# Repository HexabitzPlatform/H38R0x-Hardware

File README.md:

# H38R0x-Hardware

Hexabitz Isolated Bipolar 15V DC-DC Power Module Hardware Design

Redesign this module and check for any errors in the previous design. No MCU is required; remove UART ports.

This design must use two hexagons with a 2-layer PCB stack-up.

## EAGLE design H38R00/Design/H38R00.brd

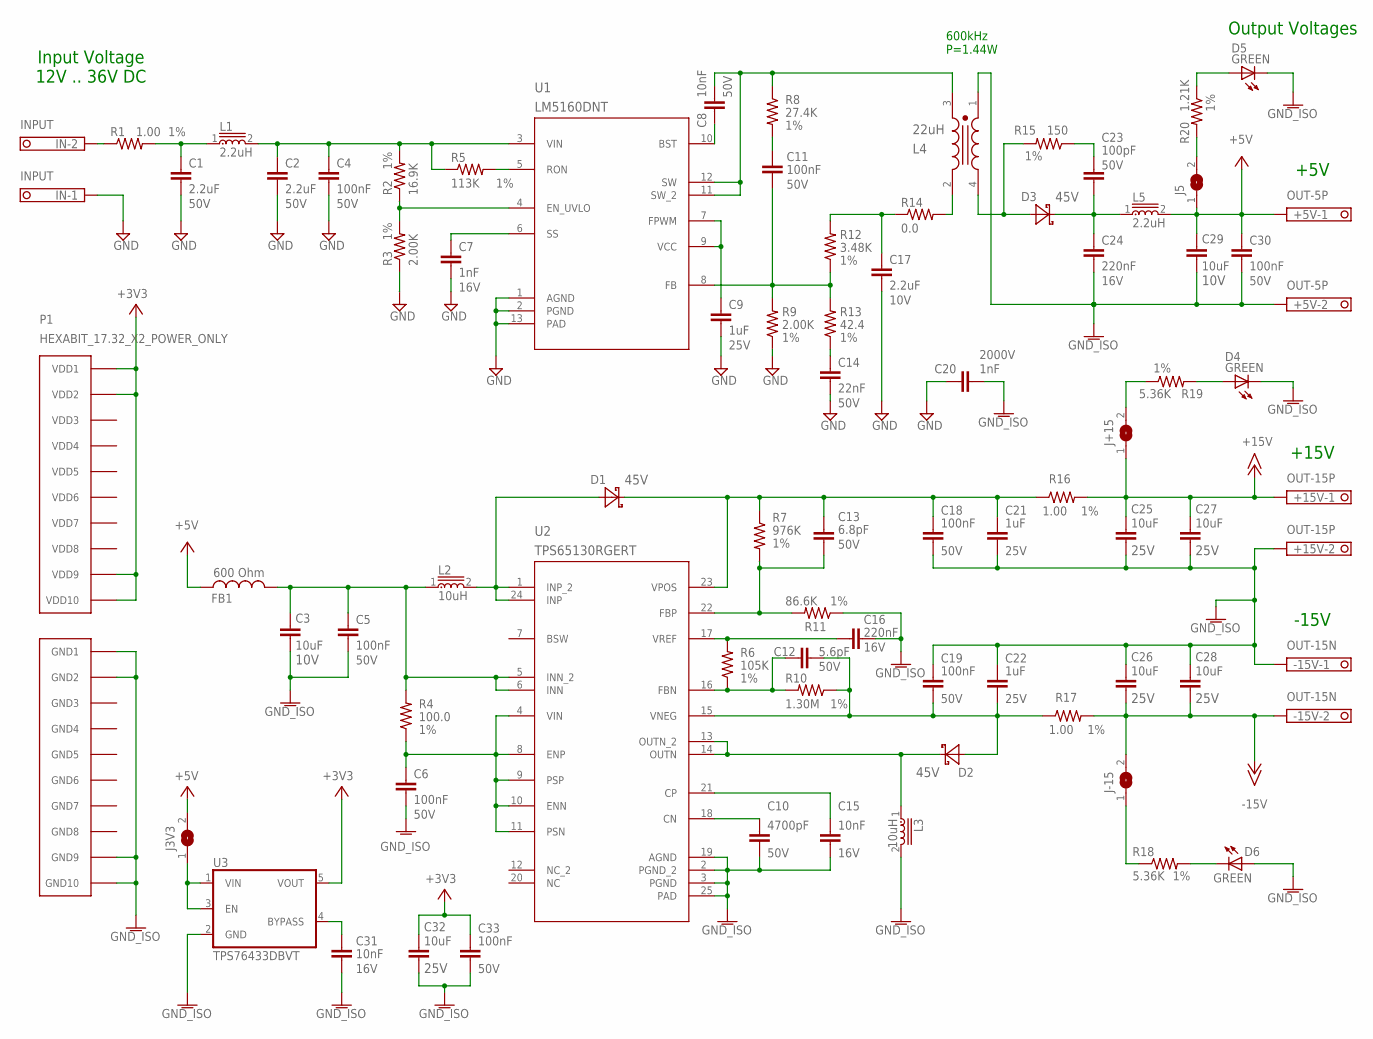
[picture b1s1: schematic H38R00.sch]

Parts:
+5V: OUT-5P; CON-PHOENIX-350_1751248
+15V: OUT-15P; CON-PHOENIX-350_1751248
-15V: OUT-15N; CON-PHOENIX-350_1751248
C1, C2: 2.2uF; C1206K; VOLTAGE 50V; MPN UMK316B7225KD-T
C3, C29: 10uF; C-0805; TOLERANCE 10%; VOLTAGE_RATING 10V; MPN 885012207026
C4, C5, C6, C11, C18, C19, C30, C33: 100nF; C-0603; TOLERANCE 10%; VOLTAGE_RATING 50V; MPN C1608X7R1H104K
C7: 1nF; C-0603; TOLERANCE 10%; VOLTAGE_RATING 16V; MPN 885012206034
C8: 10nF; C-0603; TOLERANCE 10%; VOLTAGE_RATING 50V; MPN C0603C103J5RACTU
C9, C21, C22: 1uF; C-0603; TOLERANCE 10%; VOLTAGE_RATING 25V; MPN TMK107B7105KA-T
C10: 4700pF; C-0603; TOLERANCE 10%; VOLTAGE_RATING 50V; MPN 885012206087
C12: 5.6pF; C-0603; TOLERANCE 5%; VOLTAGE_RATING 50V; MPN 06035A5R6CAT2A
C13: 6.8pF; C-0603; TOLERANCE 10%; VOLTAGE_RATING 50V; MPN 06035A6R8CAT2A
C14: 22nF; C-0603; TOLERANCE 10%; VOLTAGE_RATING 50V; MPN GRM188R71H223KA01D
C15, C31: 10nF; C-0603; TOLERANCE 10%; VOLTAGE_RATING 16V; MPN 885012206040
C16, C24: 220nF; C-0603; TOLERANCE 10%; VOLTAGE_RATING 16V; MPN 885012206048
C17: 2.2uF; C-0603; TOLERANCE 10%; VOLTAGE_RATING 10V; MPN GRM188R71A225KE15D
C20: 1nF; C1206K; VOLTAGE 2000V; MPN 202R18W102KV4E
C23: 100pF; C-0603; TOLERANCE 5%; VOLTAGE_RATING 50V; MPN C0603C101J5GACTU
C25, C26, C27, C28, C32: 10uF; C-0805; TOLERANCE 10%; VOLTAGE_RATING 25V; MPN GRM21BC71E106KE11L
D1, D2, D3: DIOD-SOD-123; SOD123; VOLTAGE_RATING_DC 45V; MPN NTS245SFT1G
D4, D5, D6: GREEN; VLMS1300-GS08
FB1: 600 Ohm; FB-0603; MPN BLM18KG601SN1D
IN: INPUT; CON-PHOENIX-350_1751248
J3V3, J5: SJ
J+15: SJ
J-15: SJ
L1, L5: 2.2uH; C-0603
L2, L3: 10uH; WUERTH_ELEKTRONIK_74404024100_0
L4: 22uH; WUERTH_ELEKTRONIK_74489430220_0
P1: HEXABIT_17.32_X2_POWER_ONLY
R1, R16, R17: 1.00; R-0603; TOLERANCE 1%; MPN CRCW06031R00FKEA
R2: 16.9K; R-0603; TOLERANCE 1%; MPN CRCW060316K9FKEA
R3, R9: 2.00K; R-0603; TOLERANCE 1%; MPN CRCW06032K00FKEA
R4: 100.0; R-0603; TOLERANCE 1%; MPN CRCW0603100RFKEA
R5: 113K; R-0603; TOLERANCE 1%; MPN CRCW0603113KFKEA
R6: 105K; R-0603; TOLERANCE 1%; MPN CRCW0603105KFKEA
R7: 976K; R-0603; TOLERANCE 1%; MPN CRCW0603976KFKEA
R8: 27.4K; R-0603; TOLERANCE 1%; MPN CRCW060327K4FKEA
R10: 1.30M; R-0603; TOLERANCE 1%; MPN CRCW06031M30FKEA
R11: 86.6K; R-0603; TOLERANCE 1%; MPN CRCW060386K6FKEA
R12: 3.48K; R-0603; TOLERANCE 1%; MPN CRCW06033K48FKEA
R13: 42.4; R-0603; TOLERANCE 1%; MPN CRCW060342R2FKEA
R14: 0.0; R-0603; TOLERANCE 5%; MPN ERJ-3GEY0R00V
R15: 150; R-0603; TOLERANCE 1%; MPN CRCW0603150RFKEA
R18, R19: 5.36K; R-0603; TOLERANCE 1%; MPN CRCW06035K36FKEA
R20: 1.21K; R-0603; TOLERANCE 1%; MPN CRCW06031K21FKEA
U1: LM5160DNT; DNT0012B
U2: TPS65130RGERT; RGE0024B_NV
U3: TPS76433DBVT; SOT25

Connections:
+3V3: C32.1, C33.1, P1.PAD_PU11 (VDD1), P1.PAD_PU12 (VDD2), P1.PAD_PU19 (VDD9), P1.PAD_PU20 (VDD10), U3.5 (VOUT)
+5V: +5V.1, C29.1, C30.1, FB1.1, J3V3.2, J5.1, L5.2
+15V: +15V.1, C25.1, C27.1, J+15.1, R16.2
-15V: -15V.2, C26.2, C28.2, J-15.2, R17.2
GND: C1.2, C2.2, C4.2, C7.2, C9.2, C14.2, C17.2, C20.1, IN.1, R3.1, R9.1, U1.1 (AGND), U1.2 (PGND), U1.13 (PAD)
GND3: P1.PAD_PD13 (GND3)
GND4: P1.PAD_PD14 (GND4)
GND5: P1.PAD_PD15 (GND5)
GND6: P1.PAD_PD16 (GND6)
GND7: P1.PAD_PD17 (GND7)
GND8: P1.PAD_PD18 (GND8)
IGND: +5V.2, +15V.2, -15V.1, C3.2, C5.2, C6.2, C10.2, C15.2, C16.2, C18.2, C19.1, C20.2, C21.2, C22.1, C24.2, C25.2, C26.1, C27.2, C28.1, C29.2, C30.2, C31.2, C32.2, C33.2, D4.C, D5.C, D6.A, L3.2, L4.1, P1.PAD_PD11 (GND1), P1.PAD_PD12 (GND2), P1.PAD_PD19 (GND9), P1.PAD_PD20 (GND10), R11.1, U2.2 (PGND_2), U2.3 (PGND), U2.19 (AGND), U2.25 (PAD), U3.2 (GND)
unnamed: IN.2, R1.1
unnamed: C1.1, L1.1, R1.2
unnamed: C2.1, C4.1, L1.2, R2.2, R5.1, U1.3 (VIN)
unnamed: R5.2, U1.5 (RON)
unnamed: R2.1, R3.2, U1.4 (EN_UVLO)
unnamed: C7.1, U1.6 (SS)
unnamed: C8.2, L4.3, R8.1, U1.11 (SW_2), U1.12 (SW)
unnamed: C8.1, U1.10 (BST)
unnamed: C9.1, U1.7 (FPWM), U1.9 (VCC)
unnamed: C11.2, R9.2, R12.1, R13.2, U1.8 (FB)
unnamed: C11.1, R8.2
unnamed: C17.1, R12.2, R14.1
unnamed: L4.2, R14.2
unnamed: C14.1, R13.1
unnamed: C23.2, C24.1, D3.2 (C), L5.1
unnamed: D3.1 (A), L4.4, R15.2
unnamed: C23.1, R15.1
unnamed: C3.1, C5.1, FB1.2, L2.1, R4.2, U2.5 (INN_2), U2.6 (INN)
unnamed: J5.2, R20.2
unnamed: D5.A, R20.1
unnamed: D1.1 (A), L2.2, U2.1 (INP_2), U2.24 (INP)
unnamed: C13.2, C18.1, C21.1, D1.2 (C), R7.1, R16.1, U2.23 (VPOS)
unnamed: C6.1, R4.1, U2.4 (VIN), U2.8 (ENP), U2.9 (PSP), U2.10 (ENN), U2.11 (PSN)
unnamed: C10.1, U2.18 (CN)
unnamed: C15.1, U2.21 (CP)
unnamed: D2.2 (C), L3.1, U2.13 (OUTN_2), U2.14 (OUTN)
unnamed: C12.2, C19.2, C22.2, D2.1 (A), R10.1, R17.1, U2.15 (VNEG)
unnamed: C12.1, R6.1, R10.2, U2.16 (FBN)
unnamed: C16.1, R6.2, U2.17 (VREF)
unnamed: C13.1, R7.2, R11.2, U2.22 (FBP)
unnamed: J+15.2, R19.1
unnamed: D4.A, R19.2
unnamed: J-15.1, R18.1
unnamed: D6.C, R18.2
unnamed: C31.1, U3.4 (BYPASS)
unnamed: J3V3.1, U3.1 (VIN), U3.3 (EN)
VDD3: P1.PAD_PU13 (VDD3)
VDD4: P1.PAD_PU14 (VDD4)
VDD5: P1.PAD_PU15 (VDD5)
VDD6: P1.PAD_PU16 (VDD6)
VDD7: P1.PAD_PU17 (VDD7)
VDD8: P1.PAD_PU18 (VDD8)

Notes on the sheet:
Input Voltage 12V .. 36V DC
600kHz P=1.44W
Output Voltages
+5V
+15V
-15V

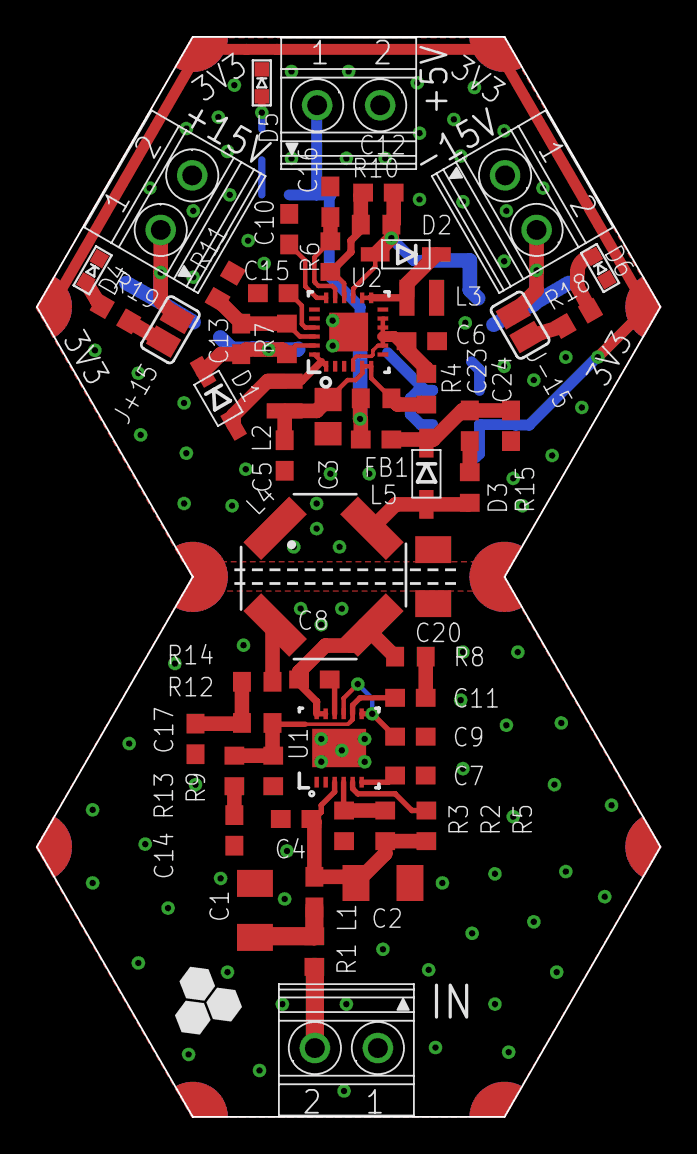
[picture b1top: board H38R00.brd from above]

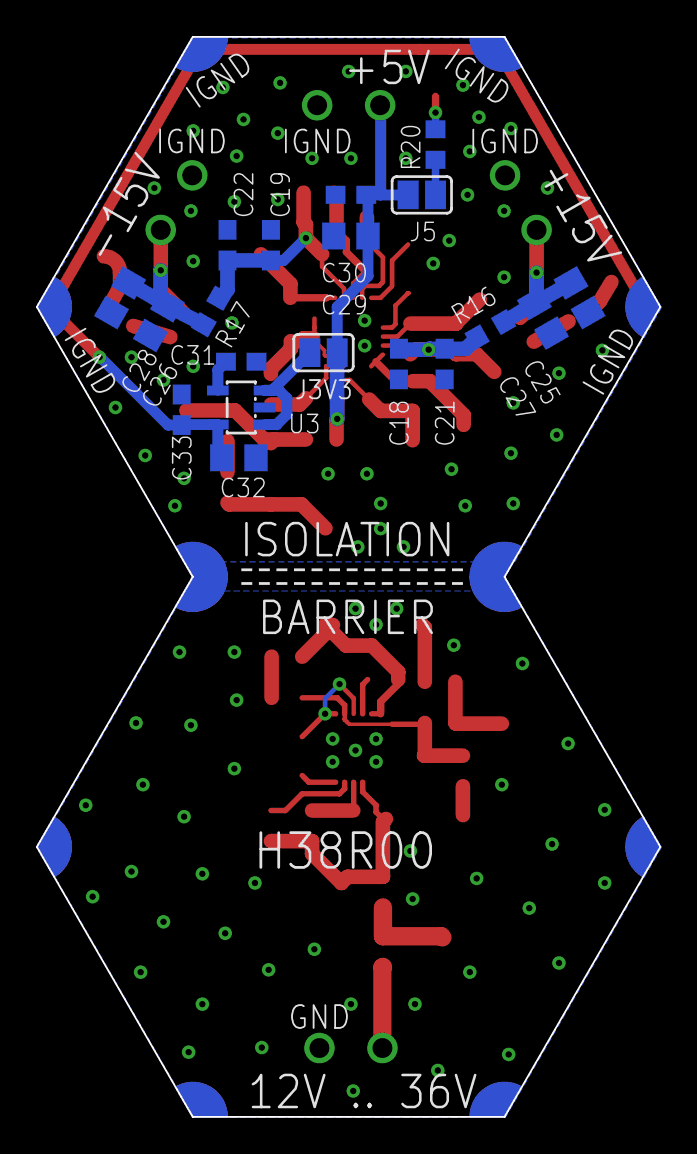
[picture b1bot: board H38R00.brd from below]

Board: 2 copper layers, 34.6 x 60.0 mm, 77 parts (19 on the bottom side), 42 nets.

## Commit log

2020-01-13 Adding template project + x2 power-only connector
2020-01-15 Added main ICs and some passives
2020-01-16 Finished the buck part
2020-01-17 Finished schematics
2020-01-18 Renumber components Update transformer package Place connectors and half components
2020-01-21 All components placed inside board!
2020-01-22 added 3.3V LDO on 5V output
2020-01-22 Arranged most silkscreen Added labels
2020-01-23 Finished arranging silkscreen Added polygons and isolation barrier
2020-01-30 Route most of top layer and raarrange some components
2020-02-08 Via stitching. Ready for DRC
2020-02-08 DRC OK
2020-02-08 Generate gerberm pick n place and schematics
2020-02-08 Adding BOM Updating some params Ready for release Rev0
2020-02-15 Update BOM
2020-07-11 1-Nc pin (12) at "Tps65130" ic was Grounded due to make GND near to "L3" 2-blank space under frequencies components was made as much as we can 3-Labels on the input connector (Vin + Gnd + Vin=12..36 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
2020-08-23 New revision...
    output files is generated
2025-10-16 The Altium template has been added.
